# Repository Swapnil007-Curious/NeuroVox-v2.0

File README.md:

# NeuroVox v2.0

A forearm band that reads tiny muscle signals and turns them into spoken sentences. It's for people who can't talk anymore (ALS, stroke, vocal cord damage, some spinal injuries) but can still twitch a muscle in their forearm, which turns out to be most of them for a long time.

**Hardware:** ₹10,000
**Software (companion website + AI voice):** ₹20,000 per year

For comparison, commercial AAC devices (eye trackers, switch boards, dedicated speech generators) go for roughly ₹85,000 to well over ₹12 lakh, and most of them need a clinician to set up. That gap is basically the whole reason this project exists.

---

## Why

Stephen Hawking ran his whole speech system off one cheek muscle. The idea here is the same, just moved to the forearm and built out of parts you can actually order from LCSC.

The part I cared about most is the output. A lot of cheap assistive projects stop at "the device can say yes or no." That's not much better than a call bell. NeuroVox only classifies four gestures on the board, but the companion website hands that label to an LLM along with the time of day, who the person is talking to, and what was just said, and gets back a real sentence. Same YES gesture can come out as "Yes, the pain's still there" or "Yes, let's go outside" depending on what was asked a second ago.

---

## How it works

1. **Electrodes.** Four standard 2" x 2" TENS pads stick on the skin. Two go over the flexor digitorum superficialis (inner forearm) and two over the extensor digitorum (outer forearm). Leads plug into the board through JST-SH connectors. The pads are NOT built into the enclosure, I tried that early on and it doesn't work because the two muscle groups are on opposite sides of the arm.
2. **Analog front end.** Four AD8232s amplify and filter the microvolt signals. An INA333 does extra differential conditioning on two channels.
3. **ADC.** An ADS1299 (24 bit, biosignal grade) samples all four channels over SPI. Way better resolution than the ESP32's own ADC.
4. **Classification on the board.** The ESP32-S3 smooths each channel into an envelope, compares it to a threshold that adapts to the person over time, and counts pulses. 1 pulse = YES, 2 = NO, 3 = HELP, 4 or more = WAIT. A BNO055 IMU throws out samples when the arm moves suddenly so a wave of the hand doesn't get read as a gesture.
5. **Bluetooth.** The gesture label plus a confidence score goes out over BLE (something like `CH1:YES:91%`).
6. **Sentence + voice.** The companion website receives it, gets a sentence from Claude, shows it on screen and speaks it out loud in the chosen language (English, Hindi, Marathi, Tamil, Bengali and a few others).

Muscle twitch to spoken sentence is meant to land in under two seconds, most of that is network time not the board.

---

## The board

2 layer FR4, **220mm x 50mm**, designed in KiCad 8. It's long and skinny on purpose so it runs along the forearm instead of across it.

The board is split into three zones along its length:

| Zone | Position | What's in it |
|---|---|---|
| Power | 0 to 60mm | MCP73831 Li-Po charger, TPS61023 boost (5V), AMS1117 3.3V regulator, USB-C input |
| Analog | 60 to 150mm | 4x AD8232, ADS1299, INA333, electrode connectors J3 to J6 |
| Digital | 150 to 220mm | ESP32-S3-WROOM-1-N8, BNO055 IMU, DRV2605L haptic driver, MAX98357A audio amp, RGB LEDs, buzzer, programming header J7 |

Analog and digital grounds are separate pours that only meet at one point, a ferrite bead right where the analog zone ends. The ESP32's antenna sits at the right edge with no copper under it.

**Why 220mm and not 200mm:** the first version was 200mm and the analog section was too packed. There was one ground connection near the instrumentation amp that just could not be routed, I checked it with an exhaustive pathfinding run, not just the autorouter giving up. Stretching the board 20mm and giving the analog zone 90mm instead of 65mm fixed it. If you fork this and want it smaller, expect that fight again.

### Pin map (real hardware)

| Function | GPIO |
|---|---|
| ADS1299 SPI CLK / MOSI / MISO / CS / DRDY | 10, 11, 12, 13, 14 |
| I2C SDA / SCL (BNO055, DRV2605L) | 21, 18 |
| Haptic enable | 8 |
| I2S to MAX98357A | 15, 16, 17 |
| Status LEDs | 2, 4, 47 |
| Buzzer | 48 |

### Fab notes

- You need **Standard PCBA** at JLCPCB, not Economic. The ESP32-S3 module, the MAX98357A (WLCSP) and the DRV2605L (DSBGA) aren't hand solderable at any sane yield.
- Standard PCBA adds temporary 5mm rails on the long edges for the pick and place machine. Ask for V-scores so they snap off and you get the real 220 x 50mm board back.
- The DRV2605L's center ball needs via-in-pad to escape. Mention it in the order notes.
- Gerbers and the full `.kicad_pcb` are in `/PCB`. I didn't make a separate schematic file for this revision.

---

## Firmware

FreeRTOS on the ESP32-S3, four tasks so the Bluetooth stack can't mess up sample timing:

| Task | Core | Priority | Job |
|---|---|---|---|
| ADC sampling | 0 | 5 | reads all 4 channels into a ring buffer |
| Gesture classifier | 1 | 3 | envelope, adaptive threshold, pulse counting, confidence |
| BLE dispatcher | 1 | 1 | sends gesture strings to the website |
| IMU monitor | 1 | 1 | flags motion over 1.5G so those samples get dropped |

A few details that matter for accuracy:

- Envelope is an exponential moving average (alpha 0.05).
- Contractions shorter than 30ms are ignored, they're almost always noise.
- A gesture only gets confirmed after 400ms of quiet, so a slow double pulse doesn't get read as two singles.
- The threshold for each channel updates off a rolling average of recent peaks, because signal strength changes person to person and also drifts for the same person as muscles get tired. A threshold set on day one is wrong by day thirty, especially with something progressive like ALS.
- All four channels are treated the same. An older board revision had a ground problem on two channels and the firmware briefly weighted them differently, that got removed once the redesign fixed the actual problem.

BLE service UUID: `180d1000-1234-1000-8000-00805f9b34fb`
Characteristic: `2a371000-1234-1000-8000-00805f9b34fb`
Device name: `NeuroVox-v2`

**Current state, honestly:** the firmware in `/FIRMWARE` is a validation build. It runs the full classification pipeline against potentiometers standing in for the EMG front end and an MPU6050 standing in for the BNO055, which let me test the logic without waiting on boards. Flip `SIM_BUILD` to false for hardware. The piece still left is swapping the analog reads for a proper SPI driver talking to the ADS1299 and moving I2C to GPIO21/18. That happens when the assembled boards are back.

**On accuracy:** my target is around 88 to 90% gesture accuracy after a short per person calibration (about 10 contractions per gesture), tested seated with the arm resting. I haven't measured that on real muscle yet because the boards aren't made yet, so please don't quote it as a result. When I test I'll report each channel separately and then combined.

---

## Enclosure

Two part snap fit, no screws holding the halves together (four M2 screws just hold the PCB to standoffs inside the top shell).

| File | Size | Notes |
|---|---|---|
| `TOP.stl` | 224 x 54 x 10mm | rigid shell, cutouts for USB-C, programming header, speaker grille, LED window, buzzer, vent slots, antenna window thinned to 1mm |
| `BOTTOM.stl` | 224 x 94.4 x 9.8mm | the skin side, strap wings stick out 20mm each side, cable clips for the electrode leads, battery bay |
| `FULL.stl` | 224 x 94.4 x 16mm | both halves together, for viewing. It isn't watertight because two meshes are combined, that's expected |

0.3mm interference lip, four alignment pegs. So the full width with strap wings is about 94mm, not 54mm, keep that in mind.

**Print it in:** PETG for the top (ABS warps badly at 224mm long on an open printer), TPU 95A for the bottom since it sits on skin for hours and the strap wings need to flex. Don't use PLA, it gets soft around 60C and tacky against skin.

---

## Bill of materials

Main parts:

| Part | LCSC |
|---|---|
| ESP32-S3-WROOM-1-N8 | C2913198 |
| ADS1299IPAGR | C476817 |
| AD8232ACPZ-R7 (x4) | C43216 |
| INA333AIDGKR | C19450 |
| BNO055BST | C93216 |
| DRV2605LYZFR | C2869341 |
| MAX98357AEWL+T | C2682619 |
| MCP73831T-2ACI/OT | C424093 |
| TPS61023DRLR | C919459 |
| AMS1117-3.3 | C6186 |
| USB-C TYPE-C-31-M-12 | C165948 |
| JST-SH 3 pin (x4, electrodes) | C160403 |
| JST-PH 2 pin (battery) | C265016 |

Bought separately: 5000mAh 3.7V Li-Po with a JST-PH lead, a pack of 2" x 2" TENS pads (you need 8 per session), TENS snap leads, a 25mm strap with velcro or a buckle, and the printed shells.

Two things to watch before ordering:
- **FB1 ferrite bead:** the exact BLM18PG601SN1D wasn't confirmed on LCSC. BLM18AG601SN1D (C19330) is the same value and package but a different current series, check the datasheet first.
- **BZ1 buzzer:** the PUI SMT-0825-S-4-R isn't on LCSC at all. Get it from DigiKey or Mouser and solder it after, it's just two pads.
- Also the ADS1299 is the expensive one and the BNO055 has a history of going out of stock. Check live stock right before you order.

---

## Software side

There's no separate phone app. Everything runs inside the NeuroVox website.

- The public site explains the device. The actual companion app is behind an activation code that comes in the box, so only owners can get in.
- Bluetooth runs through the Web Bluetooth API. Works in Chrome on Android and desktop. Doesn't work on iPhone Safari, that's an Apple limitation, there's a demo mode for that case.
- Speech uses the browser's built in text to speech, so no extra voice API is needed.
- The Claude API call goes through a server side function so the API key never sits in the browser.
- Inside the app: live gesture and sentence display, conversation history with translation, charts (hourly activity, weekly trend, gesture mix, live signal trace), device status and a signal test.

The software subscription (₹20,000 a year) covers the AI sentence generation, which is a real running cost per message, plus updates.

---

## What's done and what isn't

Done:
- PCB layout, fab ready
- Enclosure, both halves, printable
- Firmware classification pipeline, tested in simulation
- BOM with verified part numbers
- Companion website with the gated app

Not done yet:
- Boards aren't fabricated, waiting on funding
- ADS1299 SPI driver for the real board
- Real accuracy numbers on actual people
- Voice cloning (record someone's voice before they lose it, then speak in it later). The hook is in the code but nothing's connected
- A two step gesture menu (pick a category like body, food, comfort, emergency, then pick inside it) so people can say more specific things

---

## Not a medical device

NeuroVox is a student research project. It isn't certified or clinically validated, and it shouldn't replace an AAC device a clinician has prescribed or be the only way someone calls for help in an emergency. If you're a caregiver please stay involved and don't rely only on what the band says.

---

## Links

- Main repo: https://github.com/Swapnil007-Curious/NeuroVox-v2.0
- CAD: https://github.com/Swapnil007-Curious/NeuroVox-v2.0/tree/main/CAD
- PCB: https://github.com/Swapnil007-Curious/NeuroVox-v2.0/tree/main/PCB
- Firmware: https://github.com/Swapnil007-Curious/NeuroVox-v2.0/tree/main/FIRMWARE

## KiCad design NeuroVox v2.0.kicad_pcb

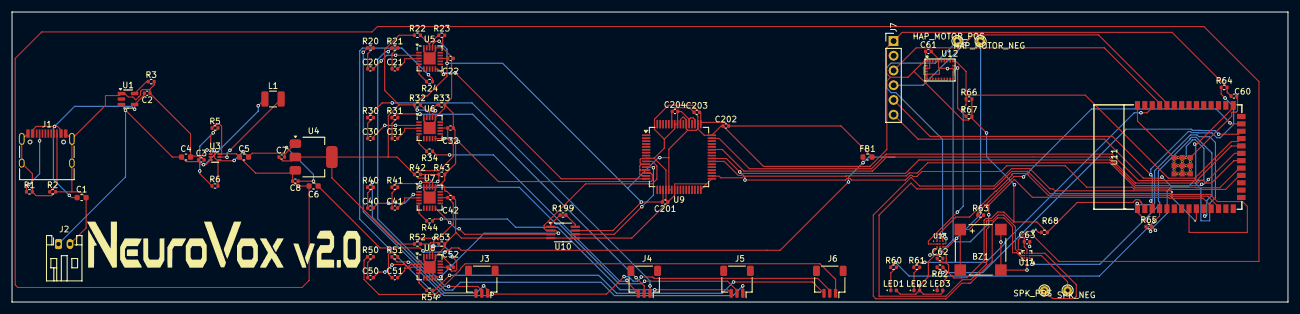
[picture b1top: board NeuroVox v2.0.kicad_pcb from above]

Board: 2 copper layers, 220.0 x 50.0 mm, 93 parts (0 on the bottom side), 81 nets.

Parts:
BZ1: BUZZER_SMD_5V; PUIAudio_SMT_0825_S_4_R
C1, C4, C5, C6: 10uF; C_0603_1608Metric
C2, C3, C7, C8, C22, C32, C42, C52, C60, C61, C62, C63, C201, C202, C203, C204: 100nF; C_0402_1005Metric
C20, C21, C30, C31, C40, C41, C50, C51: 10nF; C_0402_1005Metric
FB1: BLM18PG601SN1D; L_0603_1608Metric
HAP_MOTOR_NEG: HAP_MOTOR_NEG; TestPoint_THTPad_D1.5mm_Drill0.7mm
HAP_MOTOR_POS: HAP_MOTOR_POS; TestPoint_THTPad_D1.5mm_Drill0.7mm
J1: USB_C_Receptacle_Power; USB_C_Receptacle_HRO_TYPE-C-31-M-12
J2: Battery_JST_PH_2p; JST_PH_S2B-PH-K_1x02_P2.00mm_Horizontal
J3: Electrode_CH1; JST_SH_SM03B-SRSS-TB_1x03-1MP_P1.00mm_Horizontal
J4: Electrode_CH2; JST_SH_SM03B-SRSS-TB_1x03-1MP_P1.00mm_Horizontal
J5: Electrode_CH3; JST_SH_SM03B-SRSS-TB_1x03-1MP_P1.00mm_Horizontal
J6: Electrode_CH4; JST_SH_SM03B-SRSS-TB_1x03-1MP_P1.00mm_Horizontal
J7: PROG_HEADER; PinHeader_1x06_P2.54mm_Vertical
L1: 2.2uH; L_1210_3225Metric
LED1: LED_RED; LED_0402_1005Metric
LED2: LED_GREEN; LED_0402_1005Metric
LED3: LED_BLUE; LED_0402_1005Metric
R1, R2: 5.1k; R_0402_1005Metric
R3, R64, R65: 10k; R_0402_1005Metric
R5: 40k; R_0402_1005Metric
R6: 20k; R_0402_1005Metric
R20, R21, R22, R23, R30, R31, R32, R33, R40, R41, R42, R43, R50, R51, R52, R53: 10M; R_0402_1005Metric
R24, R34, R44, R54: 330k; R_0402_1005Metric
R60, R61, R62, R63: 1k; R_0402_1005Metric
R66, R67: 4.7k; R_0402_1005Metric
R68, R199: 100k; R_0402_1005Metric
SPK_NEG: SPK_NEG; TestPoint_THTPad_D1.5mm_Drill0.7mm
SPK_POS: SPK_POS; TestPoint_THTPad_D1.5mm_Drill0.7mm
U1: MCP73831T-2ACI/OT; SOT-23-5
U3: TPS61023DRLR; SOT-563
U4: AMS1117-3.3; SOT-223
U5, U6, U7, U8: AD8232ACPZ-R7; LFCSP-20-1EP_4x4mm_P0.5mm_EP2.1x2.1mm
U9: ADS1299IPAGR; TQFP-64_10x10mm_P0.5mm
U10: INA333AIDGKR; MSOP-8_3x3mm_P0.65mm
U11: ESP32-S3-WROOM-1-N8; WIFIM-SMD_ESP32-S3-WROOM-1-N8
U12: BNO055BST; LGA28R50P4X10_380X520X100
U13: DRV2605LYZFR; DRV2605LYZFR_DSBGA9
U14: MAX98357AEWL+T; BGA9N40P3X3_134X143X69N

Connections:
3V3: C7.1, C22.1, C32.1, C42.1, C52.1, C60.1, C61.1, C62.1, C201.1, C202.1, C203.1, C204.1, J7.1, R22.1, R32.1, R42.1, R52.1, R64.2, R66.2, R67.2, R68.2, U4.2, U4.4, U5.13, U5.17, U6.13, U6.17, U7.13, U7.17, U8.13, U8.17, U9.19, U9.21, U9.22, U9.48, U9.50, U9.54, U9.56, U9.59, U10.7, U11.2, U12.1, U12.3, U12.28, U13.C2
AGND: C22.2, C32.2, C42.2, C52.2, C201.2, C202.2, C203.2, C204.2, FB1.2, R23.2, R33.2, R43.2, R53.2, U5.16, U5.20, U5.21, U6.16, U6.20, U6.21, U7.16, U7.20, U7.21, U8.16, U8.20, U8.21, U9.9, U9.11, U9.13, U9.15, U9.20, U9.23, U9.32, U9.33, U9.49, U9.51, U9.53, U9.57, U9.58, U10.4, U10.5
BZ1_A: BZ1.1, BZ1.2, R63.2
BZ1_DRV: R63.1, U11.25
CC1: J1.A5, R1.1
CC2: J1.B5, R2.1
CH1_INN: C21.2, U5.3
CH1_INN_ELEC: J3.2, R21.1
CH1_INN_RC: C21.1, R21.2
CH1_INP: C20.2, U5.2
CH1_INP_ELEC: J3.1, R20.1
CH1_INP_RC: C20.1, R20.2
CH1_RLD: R24.1, U5.5
CH1_RLD_ELEC: J3.3, R24.2
CH1_VREF: R22.2, R23.1, U5.18
CH2_INN: C31.2, U6.3
CH2_INN_ELEC: J4.2, R31.1
CH2_INN_RC: C31.1, R31.2
CH2_INP: C30.2, U6.2
CH2_INP_ELEC: J4.1, R30.1
CH2_INP_RC: C30.1, R30.2
CH2_RLD: R34.1, U6.5
CH2_RLD_ELEC: J4.3, R34.2
CH2_VREF: R32.2, R33.1, U6.18
CH3_INN: C41.2, U7.3
CH3_INN_ELEC: J5.2, R41.1
CH3_INN_RC: C41.1, R41.2
CH3_INP: C40.2, U7.2
CH3_INP_ELEC: J5.1, R40.1
CH3_INP_RC: C40.1, R40.2
CH3_RLD: R44.1, U7.5
CH3_RLD_ELEC: J5.3, R44.2
CH3_VREF: R42.2, R43.1, U7.18
CH4_INN: C51.2, U8.3
CH4_INN_ELEC: J6.2, R51.1
CH4_INN_RC: C51.1, R51.2
CH4_INP: C50.2, U8.2
CH4_INP_ELEC: J6.1, R50.1
CH4_INP_RC: C50.1, R50.2
CH4_RLD: R54.1, U8.5
CH4_RLD_ELEC: J6.3, R54.2
CH4_VREF: R52.2, R53.1, U8.18
DRDY: U9.47, U11.22
EMG_OUT1: U5.10, U9.16
EMG_OUT2: U6.10, U9.14
EMG_OUT3: U7.10, U10.3
EMG_OUT4: U8.10, U9.10, U10.2
FB: R5.2, R6.1, U3.1
GND: BZ1.3, BZ1.4, C1.2, C2.2, C3.2, C4.2, C5.2, C6.2, C7.2, C8.2, C60.2, C61.2, C62.2, C63.2, FB1.1, J1.A1, J1.A12, J1.B1, J1.B12, J1.S1, J2.2, J7.2, LED1.2, LED2.2, LED3.2, R1.2, R2.2, R3.2, R6.2, R65.2, U1.1, U3.4, U4.1, U11.1, U11.40, U11.41, U12.2, U12.5, U12.6, U12.17, U12.18, U12.25, U13.B3, U14.C2
HAPTIC_EN: U11.12, U13.A1
HAP_MOTOR_NEG: HAP_MOTOR_NEG.1, U13.C3
HAP_MOTOR_POS: HAP_MOTOR_POS.1, U13.A3
I2C_SCL: R67.1, U11.11, U12.19, U13.C1
I2C_SDA: R66.1, U11.23, U12.20, U13.B2
I2S_BCLK: U11.9, U14.C1
I2S_DATA: U11.8, U14.B1
I2S_LRCLK: U11.10, U14.C3
INA_OUT: U9.12, U10.6
INA_RG: R199.1, R199.2, U10.1, U10.8
LED1_A: LED1.1, R60.2
LED1_DRV: R60.1, U11.4
LED2_A: LED2.1, R61.2
LED2_DRV: R61.1, U11.38
LED3_A: LED3.1, R62.2
LED3_DRV: R62.1, U11.24
PROG: R3.1, U1.5
SPI_CLK: U9.40, U11.18
SPI_CS: U9.39, U11.21
SPI_MISO: U9.43, U11.20
SPI_MOSI: U9.34, U11.19
SPK_NEG: SPK_NEG.1, U14.B3
SPK_POS: SPK_POS.1, U14.A3
SW: L1.2, U3.5
U11_EN: J7.5, R64.1, U11.3
U11_IO0: J7.6, R65.1, U11.27
U14_SDMODE: R68.1, U14.A1
UART0_RXD: J7.4, U11.36
UART0_TXD: J7.3, U11.37
VBAT: C3.1, C4.1, J2.1, L1.1, U1.3, U3.2, U3.3
VBUS: C1.1, C2.1, J1.A4, J1.A9, J1.B4, J1.B9, U1.4
VOUT_5V: C5.1, C6.1, C8.1, C63.1, R5.1, U3.6, U4.3, U14.A2

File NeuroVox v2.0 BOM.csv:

Designator,Footprint,Quantity,Designation,LCSC Part Number
"R20,R23,R21,R43,R53,R22,R32,R51,R30,R52,R42,R50,R31,R41,R40,R33",R_0402_1005Metric,16,10M,C25791
"C3,C61,C7,C32,C22,C2,C42,C201,C203,C62,C8,C52,C60,C204,C63,C202",C_0402_1005Metric,16,100nF,C1525
U1,SOT-23-5,1,MCP73831T-2ACI/OT,C424093
"R61,R63,R60,R62",R_0402_1005Metric,4,1k,C25879
J6,JST_SH_SM03B-SRSS-TB_1x03-1MP_P1.00mm_Horizontal,1,Electrode_CH4,C160403
"C21,C31,C51,C40,C20,C30,C41,C50",C_0402_1005Metric,8,10nF,C1514
LED2,LED_0402_1005Metric,1,LED_GREEN,C82914
U14,BGA9N40P3X3_134X143X69N,1,MAX98357AEWL+T,C2682619
U13,DRV2605LYZFR_DSBGA9,1,DRV2605LYZFR,C2869341
"R65,R3,R64",R_0402_1005Metric,3,10k,C25744
"C4,C5,C6,C1",C_0603_1608Metric,4,10uF,C19702
LED3,LED_0402_1005Metric,1,LED_BLUE,C82912
R6,R_0402_1005Metric,1,20k,C25769
U3,SOT-563,1,TPS61023DRLR,C919459
U9,TQFP-64_10x10mm_P0.5mm,1,ADS1299IPAGR,C476817
L1,L_1210_3225Metric,1,2.2uH,C168388
U10,MSOP-8_3x3mm_P0.65mm,1,INA333AIDGKR,C19450
"R54,R24,R34,R44",R_0402_1005Metric,4,330k,C25821
"U6,U8,U5,U7",LFCSP-20-1EP_4x4mm_P0.5mm_EP2.1x2.1mm,4,AD8232ACPZ-R7,C43216
J1,USB_C_Receptacle_HRO_TYPE-C-31-M-12,1,USB_C_Receptacle_Power,C165948
"R66,R67",R_0402_1005Metric,2,4.7k,C25900
U4,SOT-223,1,AMS1117-3.3,C6186
"R2,R1",R_0402_1005Metric,2,5.1k,C25917
"R68,R199",R_0402_1005Metric,2,100k,C25741
J5,JST_SH_SM03B-SRSS-TB_1x03-1MP_P1.00mm_Horizontal,1,Electrode_CH3,C160403
J7,PinHeader_1x06_P2.54mm_Vertical,1,PROG_HEADER,C37208
LED1,LED_0402_1005Metric,1,LED_RED,C128834
J3,JST_SH_SM03B-SRSS-TB_1x03-1MP_P1.00mm_Horizontal,1,Electrode_CH1,C160403
FB1,L_0603_1608Metric,1,BLM18PG601SN1D,C19330
U12,LGA28R50P4X10_380X520X100,1,BNO055BST,C93216
R5,R_0402_1005Metric,1,40k,C25832
J4,JST_SH_SM03B-SRSS-TB_1x03-1MP_P1.00mm_Horizontal,1,Electrode_CH2,C160403
J2,JST_PH_S2B-PH-K_1x02_P2.00mm_Horizontal,1,Battery_JST_PH_2p,C265016
BZ1,PUIAudio_SMT_0825_S_4_R,1,BUZZER_SMD_5V,C2763261
U11,WIFIM-SMD_ESP32-S3-WROOM-1-N8,1,ESP32-S3-WROOM-1-N8,C2913198

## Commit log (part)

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2026-06-10 README.md
2026-06-16 COMPUTER-AIDED DESIGN OF THIS PROJECT .
    THIS IS THE CAD OF THIS PROJECT . THIS MODEL INCLUDES A SPACE FOR THE PCB , BATTERY AND ELECTRODE CONNECTIONS .
2026-06-16 CAD.step
